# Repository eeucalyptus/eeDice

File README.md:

# eeDice
Super Hacky Electric Dice Board

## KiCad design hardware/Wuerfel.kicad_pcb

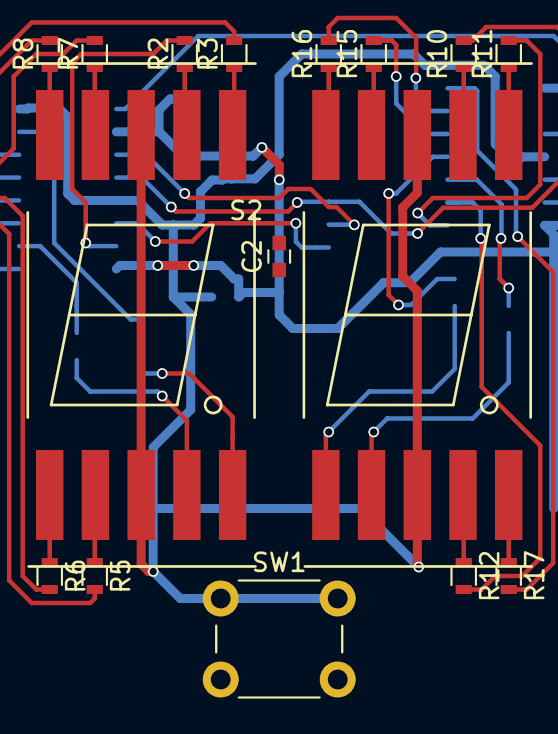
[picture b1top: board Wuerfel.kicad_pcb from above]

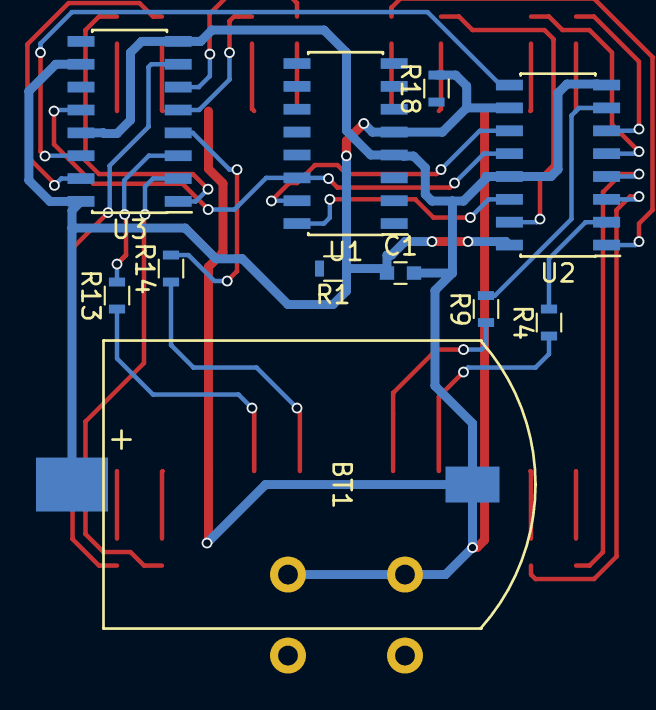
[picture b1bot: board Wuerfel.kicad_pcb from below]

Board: 2 copper layers, 27 parts (11 on the bottom side), 40 nets.

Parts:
BT1: Battery; CR2032_Halter
C1, C2: C; C_0603
R1, R2, R3, R4, R5, R6, R7, R8, R9, R10, R11, R12, R13, R14, R15, R16, R17, R18: R; R_0603
S1, S2: 7SEGM; 7-Segment
SW1: SW_PUSH; SW_PUSH_6mm
U1: EFM8BB10F8G-A-SOIC16; SOIC-16_3.9x9.9mm_Pitch1.27mm
U2, U3: 74HC595; SOIC-16_3.9x9.9mm_Pitch1.27mm

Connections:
GND: BT1.2, C1.2, S1.3, S1.8, S2.3, S2.8, SW1.1, U1.4, U2.8, U2.13, U3.8, U3.13
unnamed: C2.1, R1.2, SW1.2, U1.1
unnamed: C2.2, R18.1, U1.6
unnamed: R2.1, S1.7
unnamed: R2.2, U2.15
unnamed: R3.1, S1.6
unnamed: R3.2, U2.1
unnamed: R4.1, S1.4
unnamed: R4.2, U2.2
unnamed: R5.1, S1.2
unnamed: R5.2, U2.3
unnamed: R6.1, S1.1
unnamed: R6.2, U2.4
unnamed: R7.1, S1.9
unnamed: R7.2, U2.5
unnamed: R8.1, S1.10
unnamed: R8.2, U2.6
unnamed: R9.1, S1.5
unnamed: R9.2, U2.7
unnamed: R10.1, S2.7
unnamed: R10.2, U3.15
unnamed: R11.1, S2.6
unnamed: R11.2, U3.1
unnamed: R12.1, S2.4
unnamed: R12.2, U3.2
unnamed: R13.1, S2.2
unnamed: R13.2, U3.3
unnamed: R14.1, S2.1
unnamed: R14.2, U3.4
unnamed: R15.1, S2.9
unnamed: R15.2, U3.5
unnamed: R16.1, S2.10
unnamed: R16.2, U3.6
unnamed: R17.1, S2.5
unnamed: R17.2, U3.7
unnamed: U1.14, U2.12, U3.12
unnamed: U1.15, U2.11, U3.11
unnamed: U1.16, U2.14
unnamed: U2.9, U3.14
VCC: BT1.1, C1.1, R1.1, R18.2, U1.5, U2.10, U2.16, U3.10, U3.16

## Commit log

2018-08-03 - Changed Schematics Style - Added schematics printout pdf
